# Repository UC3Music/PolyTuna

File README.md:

PolyTuna
-----

    This is a work in progress
    
A DIY polyphonic guitar tuner pedal. With it you can check the tuning of all the strings with a single strum, saving you time when you need it most. Very useful for playing live!

This work has been developed by [Sergio Sánchez](https://github.com/SerjSanchez) as his Bachelor's Thesis, with [David Estevez](https://github.com/David-Estevez) as his advisor. The Thesis itself can be downloaded [here](https://github.com/UC3Music/PolyTuna/raw/master/Memoria.pdf) (in Spanish).

The work has three main parts:

* A preeliminary study of the guitar signal to decide the best analysis technique for the pedal. This study was made in Matlab and the sources for the study can be found in the `MATLAB Analysis` folder.
* A software implementation of the polyphonic tuner to validate the algorithms prior to the hardware implementation. This code is written in Python and contained in the `Software tuner` folder.
* A hardware implementation (i.e. the pedal itself). The firmware for the device is stored in the `Polytuna Teensy Edition` folder. The schematics can be found in the [Thesis document](https://github.com/UC3Music/PolyTuna/raw/master/Memoria.pdf). The full circuit and the PCB KiCad project can be found at [`Polytuna KiCad`](https://github.com/UC3Music/PolyTuna/tree/master/Polytuna%20KiCad) folder.

Some pictures of the prototype:
(HD images can be found [`here`](https://github.com/UC3Music/PolyTuna/tree/master/doc/img/Polytuna%20PCB%20v1%20photos/HD))

The last completed step was the creation of a first PCB prototype, shown on the images, that's fully functional as a tuner.
Currently the work is focused on improving the display software capabilities to ensure it's easily readable.

#### Author
	
* Sergio Sánchez 

#### Advisor
    
*  [David Estévez Fernández](https://github.com/David-Estevez)

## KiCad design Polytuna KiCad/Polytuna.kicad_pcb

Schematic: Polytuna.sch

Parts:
BOARD1: BOARD_TEENSY_3.1; Board_Teensy_3_1
BT1: Battery; Pin_Header_Straight_1x02_Pitch2.54mm
C1: C; C_0805
C2, C3, C6, C8: 2.2uF; C_0805
C4, C5, C7: 0.1uF; C_0805
Ct1: 0.15uF; C_0805
D1, D2, D3: LED; LED_D3.0mm
Ferrite1: 600; L_0805
IC1: AP7313-33SAG-7; SOT-23; Manufacturer_Part_Number AP7313-33SAG-7
Input1: JACK_FEMALE_STEREO_6_PINS; CONN_Jack_Female_6.35mm_THD
J1: Barrel_Jack; Barrel_Jack_CUI_PJ-102AH
J2, J3, J5: Conn_01x02; Pin_Header_Straight_1x02_Pitch2.54mm
J4: Conn_01x04; Pin_Header_Straight_1x04_Pitch2.54mm
JMP1, JMP2: 2Jumper; Miscellaneous_Solder_Jumper
Output1: JACK_FEMALE_STEREO_6_PINS; CONN_Jack_Female_6.35mm_THD
R1, R2, R3, R4, R5, R6, R7: R; R_0805
R8, R9: 2.2K; R_0805
R10: 10M; R_0805
RV1, RV2, RV3: POT_TRIM; Potentiometer_Alps_RK09K_Horizontal
SW1, SW2, SW3: SW_Push; SW_PUSH_6mm_h5mm
SW4: SW_TPDT; IceStomp_Switch_3PDT
U1: LM358; SOIC-8_3.9x4.9mm_Pitch1.27mm
U2: SGTL5000; QFN-32-1EP_5x5mm_Pitch0.5mm
U3: L7805; TO-220-3_Horizontal

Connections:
+3V3: BOARD1.26, C3.1, C4.1, C5.1, Ferrite1.2, IC1.1, J2.1, J4.3, R4.1, R8.1, R9.1, RV1.3, RV2.3, RV3.3, SW4.23, U1.8, U2.20
+5V: BOARD1.28, J3.1, U3.3 (OUT)
DC_Conv: SW4.32, U3.1 (IN)
GND: BOARD1.1, BT1.2, C3.2, C4.2, C5.2, C6.2, C7.2, C8.2, IC1.3, J1.1, J2.2, J3.2, J4.4, J5.1, JMP2.2, SW1.1, SW2.1, SW3.1, U2.1, U2.3, U2.31, U2.32, U2.33, U3.2 (GND); also elsewhere on the board
GNDA: BOARD1.27, Ct1.2, Input1.R, Input1.RS, Input1.S, Input1.SS, Input1.TS, JMP2.1, Output1.R, Output1.RS, Output1.S, Output1.SS, Output1.TS, R5.2, R6.2, R10.2, RV1.1, RV2.1, RV3.1, U1.4, U2.7
INPUT: Input1.T, SW4.21
InputStage: C1.2, SW4.31
LineIN(SGTL): C2.1, U2.14
unnamed: BOARD1.5, SW1.2
unnamed: BOARD1.6, SW2.2
unnamed: BOARD1.7, SW3.2
unnamed: BOARD1.8, R3.1
unnamed: BOARD1.9, R2.1
unnamed: BOARD1.10, R1.1
unnamed: BOARD1.16, RV3.2
unnamed: BOARD1.17, RV2.2
unnamed: BOARD1.18, RV1.2
unnamed: BT1.1, J1.3
unnamed: C1.1, R4.2, R5.1, U1.3
unnamed: C2.2, R7.1, U1.1
unnamed: C6.1, IC1.2, U2.30
unnamed: C7.1, C8.1, Ferrite1.1, U2.5
unnamed: Ct1.1, U2.10
unnamed 31: R3.2; also elsewhere on the board
unnamed 32: R2.2; also elsewhere on the board
unnamed 33: R1.2; also elsewhere on the board
unnamed: J5.2, SW4.33
unnamed: R6.1, R7.2, U1.2
Output: JMP1.2, Output1.T, SW4.11
Pin9_Teensy: BOARD1.11, U2.24
Pin11_Teensy: BOARD1.13, U2.21
Pin13_Teensy: BOARD1.15, U2.25
Pin22_Teensy: BOARD1.24, U2.26
Pin23_Teensy: BOARD1.25, U2.23
PowerIn: J1.2, SW4.22
SCL: BOARD1.21, J4.1, R9.2, U2.29
SDA: BOARD1.20, J4.2, R8.2, U2.27
SGTL_Out: JMP1.1, R10.1, U2.12

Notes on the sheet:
Polytuna Scheme v1
TEENSY BOARD
AUDIO CODEC
POWER STAGE
AUDIO I/O STAGE
POWER FLAGS
SCREEN CONNECTION
Note: VDDD (1.1V - 2.0V, 11mA Min)
EXTRA POWER OUPUTS
Maybe 1uF ??

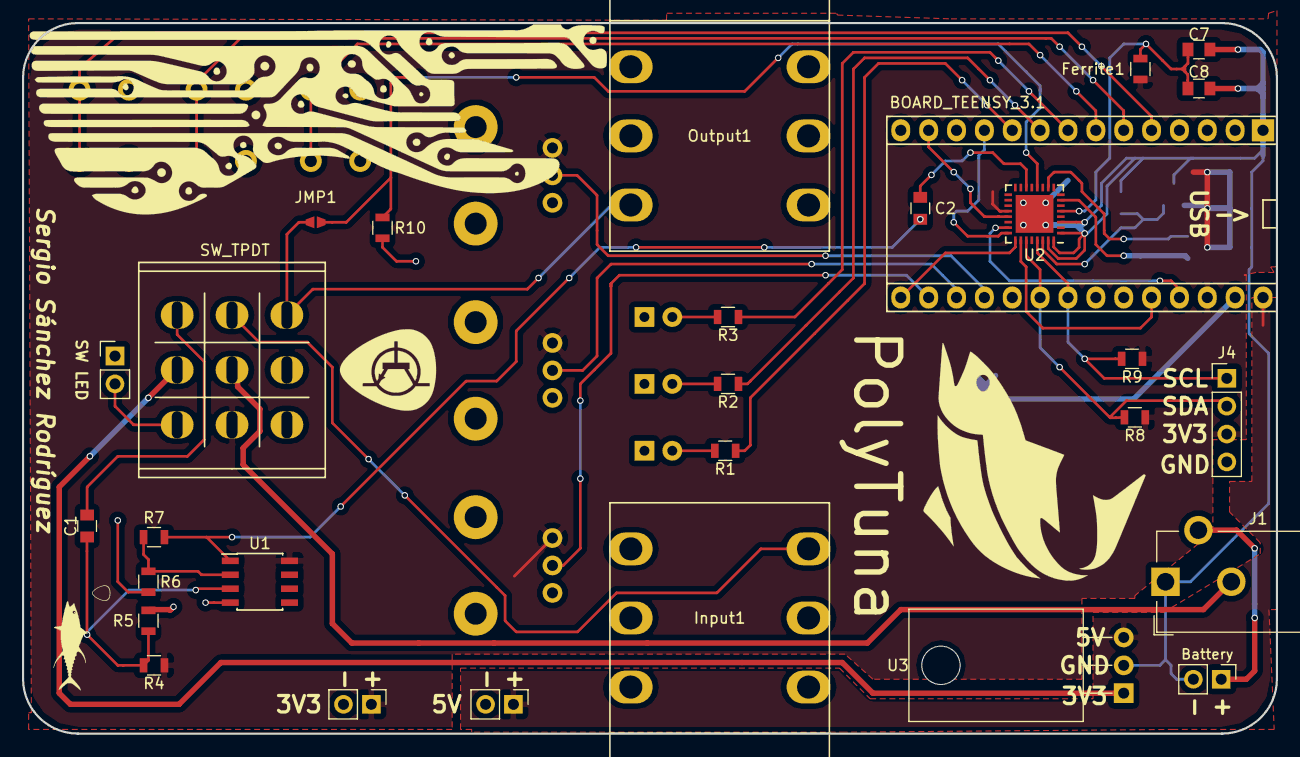
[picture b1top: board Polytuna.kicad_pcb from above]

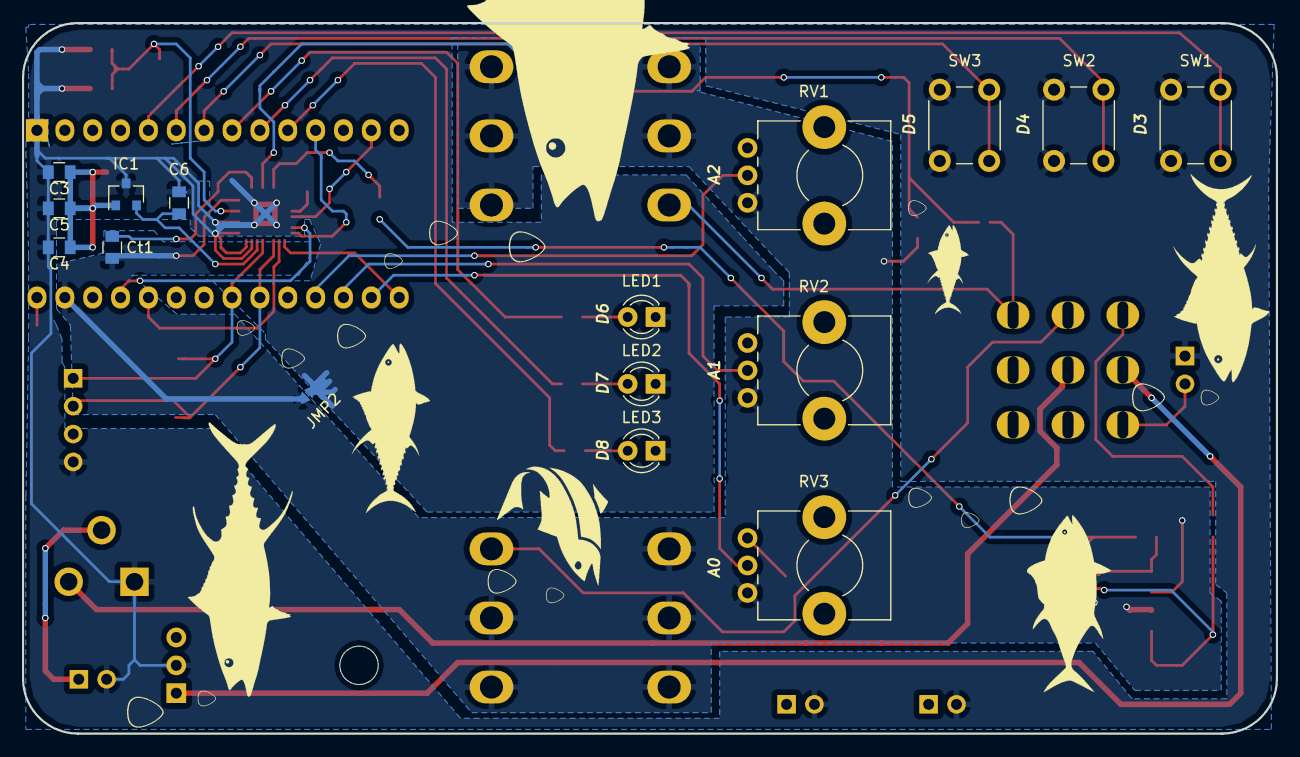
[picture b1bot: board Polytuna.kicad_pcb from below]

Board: 2 copper layers, 114.3 x 64.8 mm, 45 parts (16 on the bottom side), 38 nets.

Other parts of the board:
LED1, LED2, LED3: LED; LED_D3.0mm

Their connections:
GND: LED1.1, LED2.1, LED3.1; also elsewhere on the board
unnamed 31: LED1.2; also elsewhere on the board
unnamed 32: LED2.2; also elsewhere on the board
unnamed 33: LED3.2; also elsewhere on the board

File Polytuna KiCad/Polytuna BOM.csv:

Reference,Component,Amount,Reference,Seller,Unit Cost,Cost
Input1;Output1,Jack Female 6.35mm THD,2,568-NYS219 ,Mouser,0.724,1.448
LED1-LED3,LED Diode 3mm THD,3,,Mouser,,0
R1-R3,Resistor 0805 100R,3,,,,0
R4;R10,Resistor 0805 10M,2,,,,0
R5,Resistor 0805 2M,1,,Mouser,,0
R6,Resistor 0805 10K,1,,,,0
R7,Resistor 0805 20K,1,,,,0
R8-R9,Resistor 0805 2K2,2,,Mouser,,0
RV1-RV3,Potentiometer ALPS RK09K ?,3,,,,0
U1,Op-Amp LM358,1,,,,0
U2,Audio Codec SGTL5000 (QFN32EP),1,,,,
U3,DC/DC Converter VXO7805-500,1, 490-VXO7805-500 ,,,
J1,Barrel jack PJ-102AH ,1,490-PJ-102AH,Mouser,0.615,0.615
C1,Capacitor 0805 ceramic 10uF,1,,,,0
C2-C3;C6;C8,Capacitor 0805 ceramic 2.2uF,4,,Mouser,,0
C4;C5;C7,Capacitor 0805 ceramic 0.1uF,3,,Mouser,,0
Ct1,Capacitor 0805 ceramic 0.15uF,1,,Mouser,,0
Ferrite1,Ferrite bead 0805 600ohms,1,,,,
SW1-SW3,Switch 6x5mm,3,,Mouser,,0
SW4,Switch 3PDT,1,,Aliexpress,,
IC1,Regulator AP7313-33SAG-7,1,,,,
BOARD1,Teensy 3.1,1,-,-,,0
,,,,,Total:,2.063

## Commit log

2017-02-21 Add description
2017-02-21 Add funny picture
2017-02-21 Add simple gitignore
2017-03-17 Add the first version of the code (No comparators)
2017-03-17 Move 'def' to top
2017-03-17 Debugging audio functions
2017-03-20 Update numpy conversion to int16
2017-03-20 Add dependencies to README.md
2017-03-21 Mono tuner working. Shows frequency, string and if it's flat, high or ok
2017-03-21 First polyphonic version of the tuner. I think it doesn't work yet
2017-03-22 Small fixes to make it more pythonic
2017-03-26 6 strings printed in one line. Corrected some comparation limits.
2017-04-07 Lagrange interpolation and better terminal printing
2017-04-07 Corrected comparator
2017-08-27 Add files via upload
    Added Teensy implementation for Polytuna and the libraries to make it work. Only displays in serial. Needed to change the detection window for strings 1 & 2
2017-08-30 Erased Matplotlib imports. New detection frequency in poly mode for strings 1 & 2
2017-09-08 Comentarios mejorados y añadido el archivo mono_tuner.py
2017-09-10 Calibrated Poly tuner
2017-09-10 Add files via upload
    LCD display coded
2017-09-12 Corrected Display.
2017-09-16 Calibrated and slightly better display
2017-09-26 Add files via upload
    MATLAB files for the previous acoustic analysis
2017-10-15 Move software to dedicated folder
2017-10-15 Add pycharm folder to gitignore
2017-10-15 Add specific README.md files
2017-10-15 Add images
2017-10-15 Modify image size in README
2018-03-02 First KiCad Schematic
    Needs a DC-DC conversor, AP7313, check Teensy board connections
2018-03-03 Added some switches, LEDs and jumpers
2018-03-03 Add switches, LEDs and jumpers
2018-03-07 AP7313 Libraries
2018-03-07 Added some pwr_flags, AP7313
2018-03-08 Added i2c ports to scheme and power stage
2018-03-08 Solve power flag issues
2018-03-09 Corrected GNDA/GND and i2c pins
2018-03-09 Finished schematic
2018-03-09 Added some footprints
2018-03-12 footprint-component relation finished
2018-03-14 Started PCB
2018-03-16 Progress in routing
2018-03-16 Moar routing
2018-03-17 Moar routing x2
    Still have to add the 3pdt
2018-03-17 PCB v0.1
2018-03-23 Added some logos and changed silks
2018-03-24 PCB v1
    PCB
2018-03-24 PCB v1
2018-03-28 Added some logos
    Still in need of tunas
2018-03-28 Moar logos
2018-03-30 Changed some logos. Added a tuna
2018-03-30 MOAR TUNAS FOR EVERYBODY
2018-04-01 Added some "Pibbles" and no DRC errors
2018-04-02 PCB v1 finished
2018-04-11 Some fixes
2018-04-11 Add GERGERs
2018-04-11 Nice and round edges
2018-04-12 Changed OP's footprint
2018-04-13 GERBERs
2018-04-15 Regenerate GERBERs
2018-05-06 Added values for input stage resistors
2018-05-06 Add BOM
2018-05-07 Corrected C6 value
2018-05-14 DC-DC conversor Datasheet and PCB 3D render
2018-06-24 Some PCB V1 photos
    Everything worked nice!
2018-06-25 Organized images
2018-06-25 Renamed imgs
2018-06-25 Update README.md
    Change the old prototype images to show the new one with the PCB
2018-06-25 Update README.md
    Added images of the new prototype with the PCB
2018-06-25 Update README.md
    Updated the description
2018-06-25 Resized images
    Resized images
2018-06-26 Resized images
2019-08-12 Updated project organization
2019-08-18 Moved arrow definitions to the .c to avoid warnings.
